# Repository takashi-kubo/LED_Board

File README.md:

# LED_Board
for SummerStudy

LED:http://akizukidenshi.com/catalog/g/gI-02082/
http://akizukidenshi.com/catalog/g/gI-09975/

Register:http://akizukidenshi.com/catalog/g/gR-25151/

PushSW:http://akizukidenshi.com/catalog/g/gP-01282/

Battery:http://akizukidenshi.com/catalog/g/gP-02679/

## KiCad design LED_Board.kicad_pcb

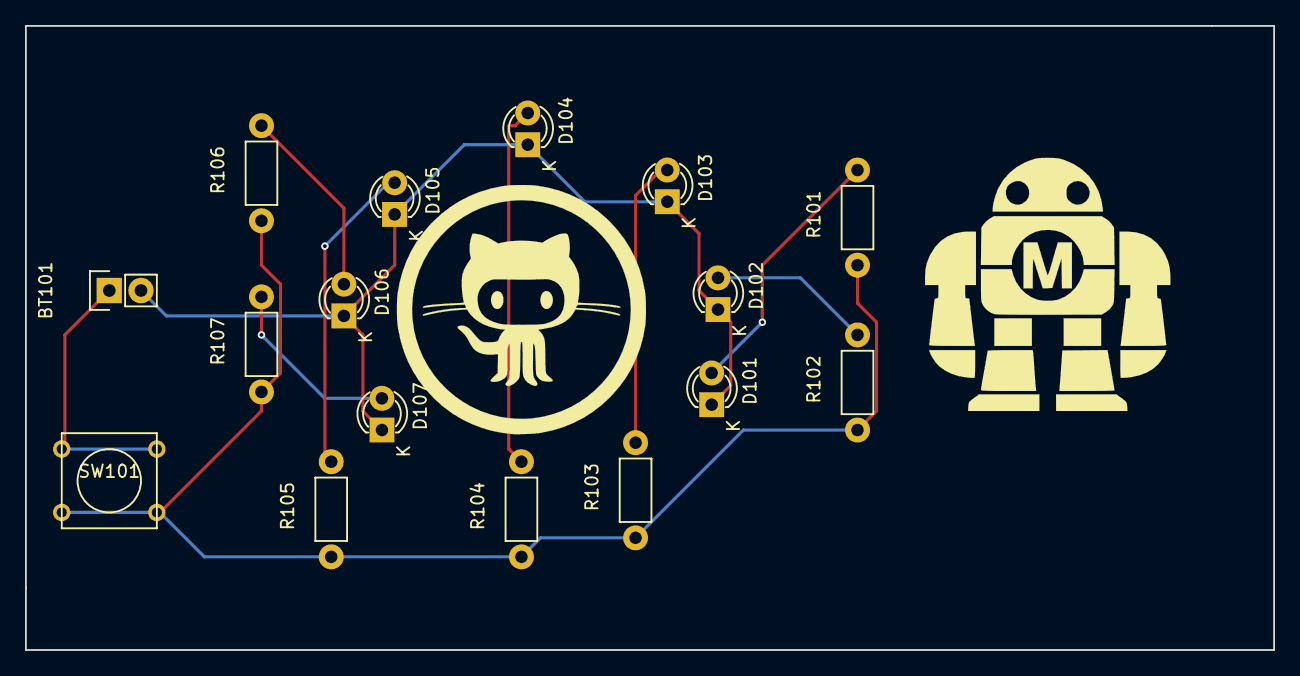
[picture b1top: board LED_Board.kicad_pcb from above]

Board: 2 copper layers, 100.0 x 50.0 mm, 16 parts (0 on the bottom side), 10 nets.

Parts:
BT101: Battery; Pin_Header_Straight_1x02
D101, D102, D103, D104, D105, D106, D107: LED; LED-3MM
R101, R102, R103, R104, R105, R106, R107: 150; Resistor_Horizontal_RM7mm
SW101: SW_PUSH; SW_PUSH_SMALL

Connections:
+BATT: R101.1, R102.1, R103.1, R104.1, R105.1, R106.1, R107.1, SW101.2
GND: BT101.2, D101.1, D102.1, D103.1, D104.1, D105.1, D106.1, D107.1
unnamed: BT101.1, SW101.1
unnamed: D101.2, R101.2
unnamed: D102.2, R102.2
unnamed: D103.2, R103.2
unnamed: D104.2, R104.2
unnamed: D105.2, R105.2
unnamed: D106.2, R106.2
unnamed: D107.2, R107.2

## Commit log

2016-07-01 Parts list
2016-07-02 add logo
2016-07-13 PCB sizze 45*95 -> 50 * 100
